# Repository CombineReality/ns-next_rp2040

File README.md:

# ns-next_rp2040
RP2040 Microcontroller board for North Star Next

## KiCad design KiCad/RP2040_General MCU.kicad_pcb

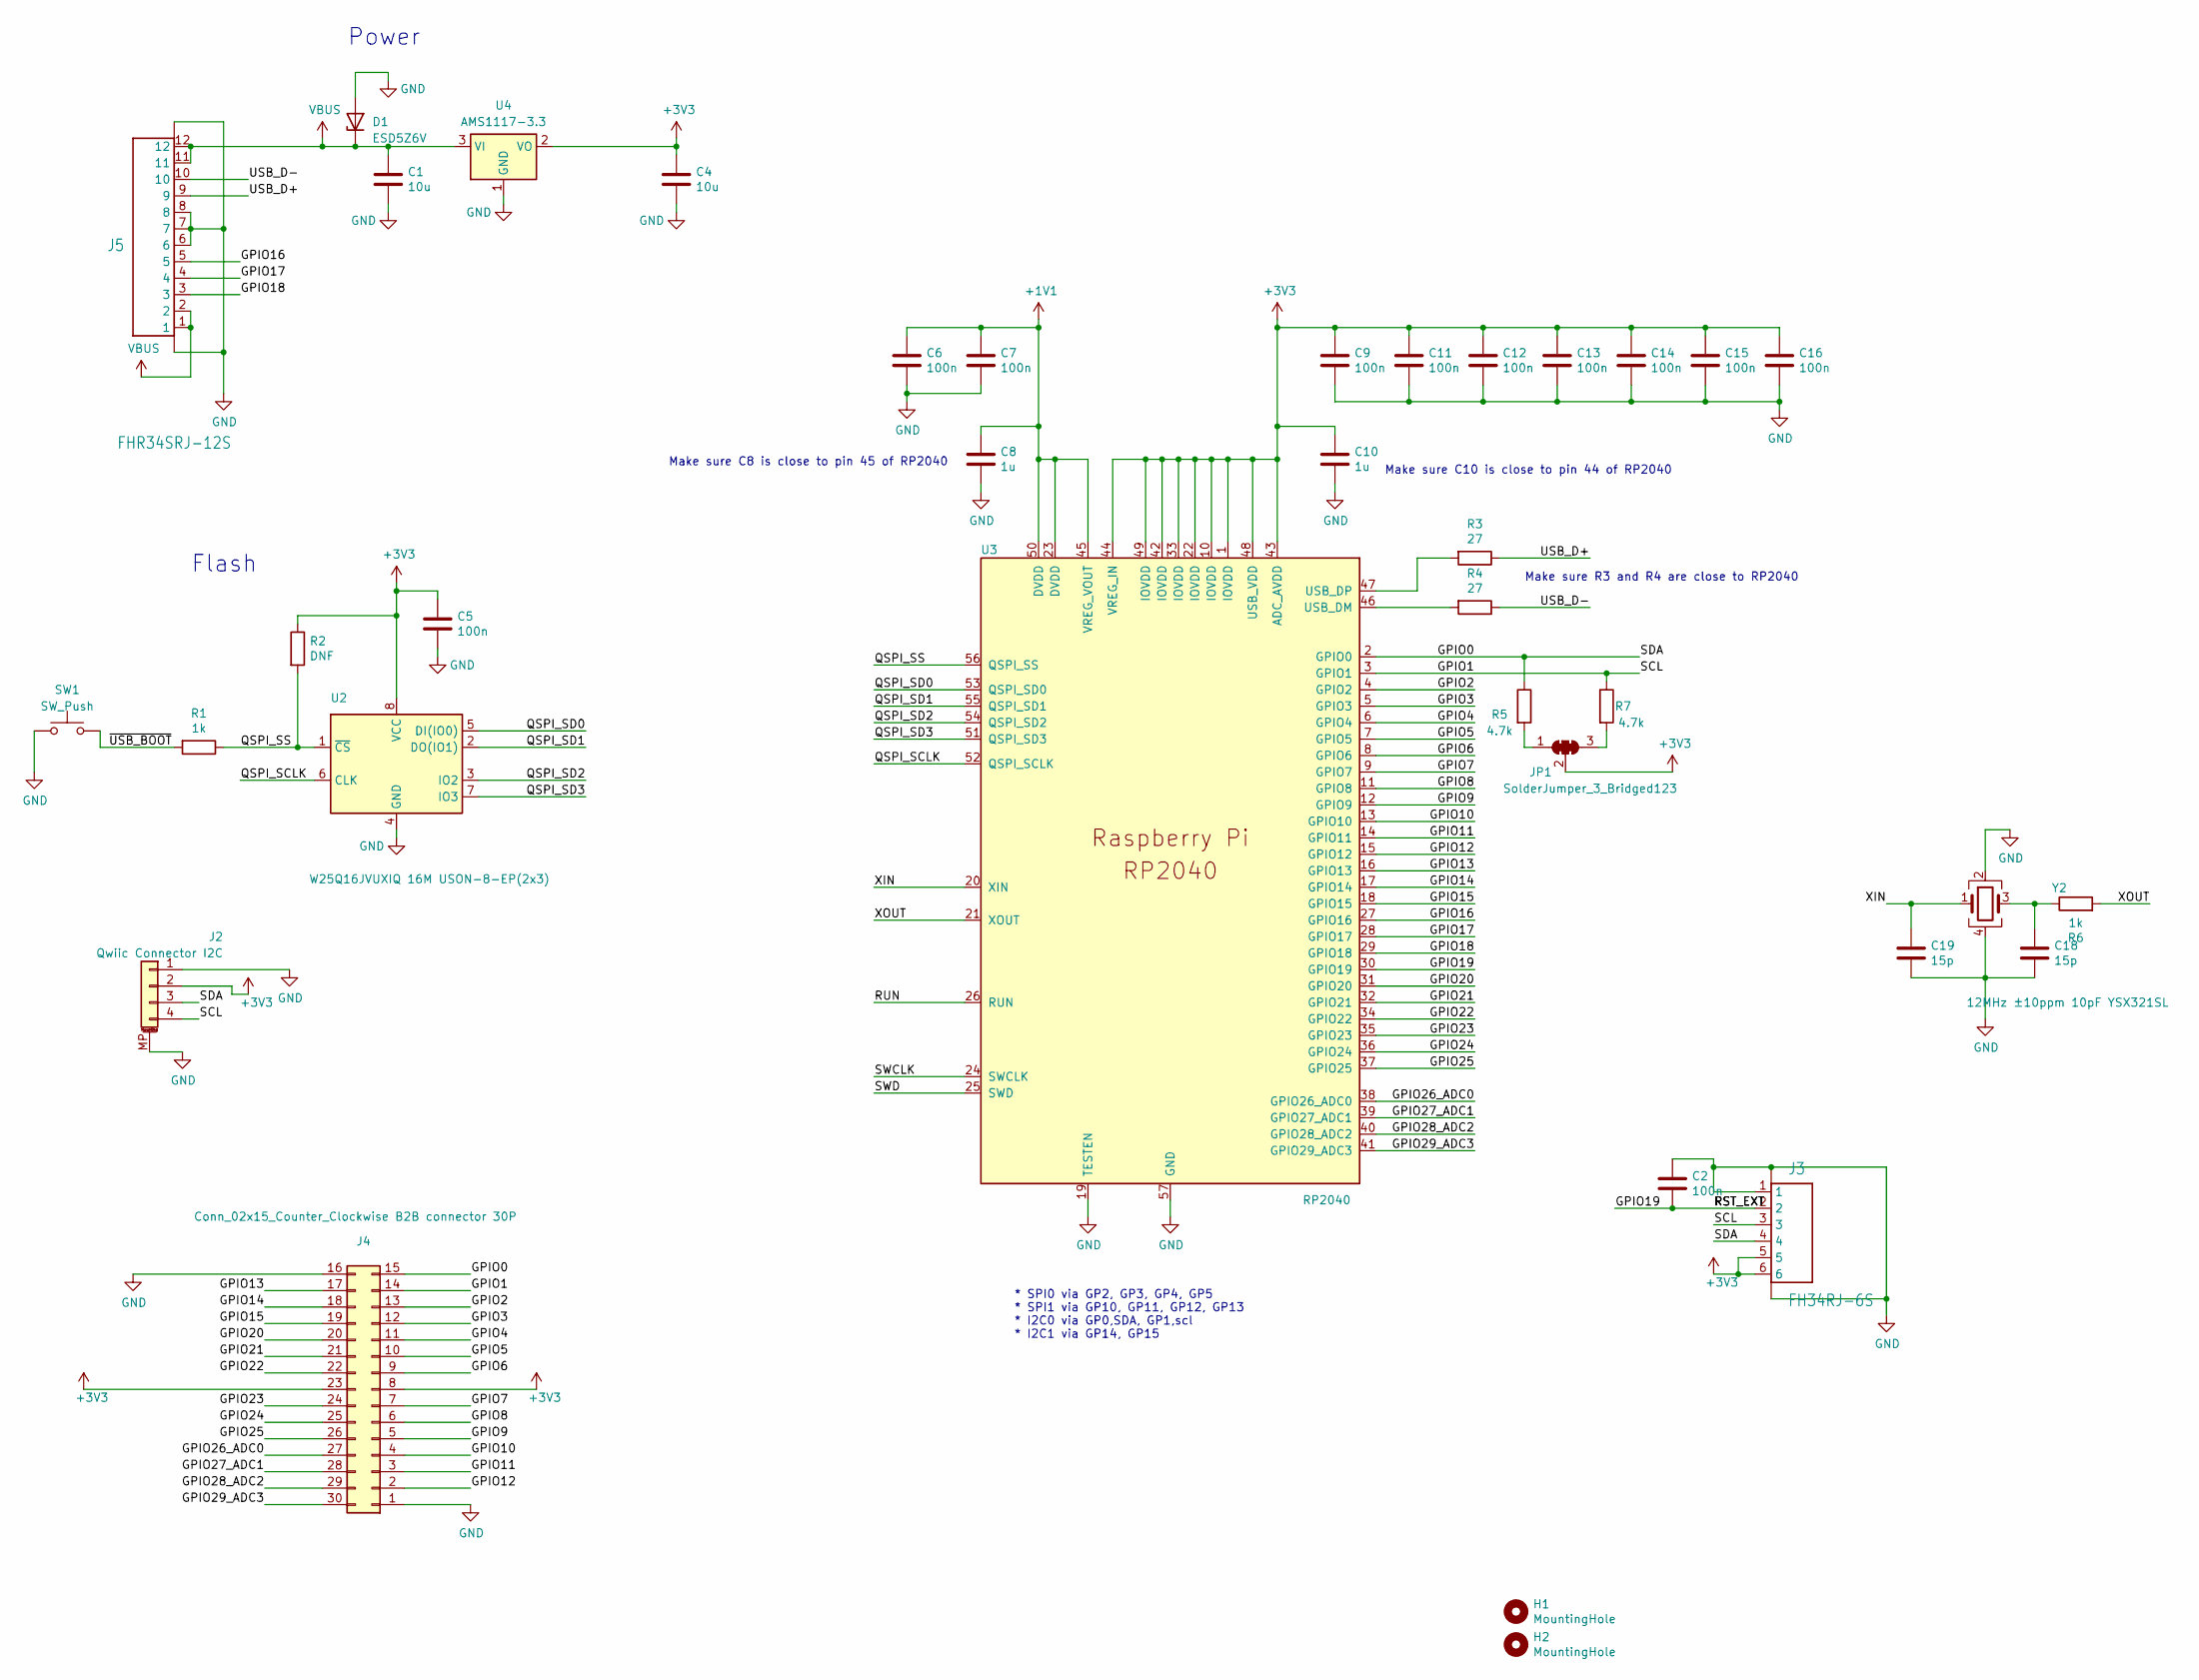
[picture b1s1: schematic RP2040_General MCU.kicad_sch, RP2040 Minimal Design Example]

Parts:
C1, C4: 10u; C_0805_2012Metric
C2, C5, C6, C7, C9, C11, C12, C13, C14, C15, C16: 100n; C_0402_1005Metric
C8, C10: 1u; C_0402_1005Metric
C18, C19: 15p; C_0402_1005Metric
D1: ESD5Z6V; D_SOD-523
H1, H2: MountingHole; MountingHole_2.2mm_M2
J2: Qwiic Connector I2C; JST_SH_SM04B-SRSS-TB_1x04-1MP_P1.00mm_Horizontal
J3: FH34RJ-6S
J4: Conn_02x15_Counter_Clockwise B2B connector 30P; BM20B(0.8)-30DS-0.4V(51)
J5: FHR34SRJ-12S; FPC-0.5-12P
JP1: SolderJumper_3_Bridged123; SolderJumper-3_P1.3mm_Open_RoundedPad1.0x1.5mm_NumberLabels
R1, R6: 1k; C_0402_1005Metric
R2: DNF; C_0402_1005Metric
R3, R4: 27; R_0402_1005Metric
R5, R7: 4.7k; C_0402_1005Metric
SW1: SW_Push; SW_Push_1P1T_NO_Vertical_Wuerth_434133025816
U2: W25Q16JVUXIQ 16M USON-8-EP(2x3); USON8_2X3MM
U3: RP2040; RP2040-QFN-56
U4: AMS1117-3.3; SOT-89-3
Y2: 12MHz ±10ppm 10pF YSX321SL; Crystal_SMD_3225-4Pin_3.2x2.5mm

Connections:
+1V1: C6.1, C7.1, C8.1, U3.23 (DVDD), U3.45 (VREG_VOUT), U3.50 (DVDD)
+3V3: C4.1, C5.1, C9.1, C10.1, C11.1, C12.1, C13.1, C14.1, C15.1, C16.1, J2.2, J3.5, J3.6, J4.8, J4.23, JP1.2 (C), R2.1, U2.8 (VCC), U3.1 (IOVDD), U3.10 (IOVDD), U3.22 (IOVDD), U3.33 (IOVDD), U3.42 (IOVDD), U3.43 (ADC_AVDD), U3.44 (VREG_IN), U3.48 (USB_VDD), U3.49 (IOVDD), U4.2 (VO)
/GPIO0: J2.3, J3.4, J4.15, R5.1, U3.2 (GPIO0)
/GPIO1: J2.4, J3.3, J4.14, R7.1, U3.3 (GPIO1)
/GPIO2: J4.13, U3.4 (GPIO2)
/GPIO3: J4.12, U3.5 (GPIO3)
/GPIO4: J4.11, U3.6 (GPIO4)
/GPIO5: J4.10, U3.7 (GPIO5)
/GPIO6: J4.9, U3.8 (GPIO6)
/GPIO7: J4.7, U3.9 (GPIO7)
/GPIO8: J4.6, U3.11 (GPIO8)
/GPIO9: J4.5, U3.12 (GPIO9)
/GPIO10: J4.4, U3.13 (GPIO10)
/GPIO11: J4.3, U3.14 (GPIO11)
/GPIO12: J4.2, U3.15 (GPIO12)
/GPIO13: J4.17, U3.16 (GPIO13)
/GPIO14: J4.18, U3.17 (GPIO14)
/GPIO15: J4.19, U3.18 (GPIO15)
/GPIO16: J5.5, U3.27 (GPIO16)
/GPIO17: J5.4, U3.28 (GPIO17)
/GPIO18: J5.3, U3.29 (GPIO18)
/GPIO19: C2.2, J3.2, U3.30 (GPIO19)
/GPIO20: J4.20, U3.31 (GPIO20)
/GPIO21: J4.21, U3.32 (GPIO21)
/GPIO22: J4.22, U3.34 (GPIO22)
/GPIO23: J4.24, U3.35 (GPIO23)
/GPIO24: J4.25, U3.36 (GPIO24)
/GPIO25: J4.26, U3.37 (GPIO25)
/GPIO26_ADC0: J4.27, U3.38 (GPIO26_ADC0)
/GPIO27_ADC1: J4.28, U3.39 (GPIO27_ADC1)
/GPIO28_ADC2: J4.29, U3.40 (GPIO28_ADC2)
/GPIO29_ADC3: J4.30, U3.41 (GPIO29_ADC3)
/QSPI_SCLK: U2.6 (CLK), U3.52 (QSPI_SCLK)
/QSPI_SD0: U2.5 (DI(IO0)), U3.53 (QSPI_SD0)
/QSPI_SD1: U2.2 (DO(IO1)), U3.55 (QSPI_SD1)
/QSPI_SD2: U2.3 (IO2), U3.54 (QSPI_SD2)
/QSPI_SD3: U2.7 (IO3), U3.51 (QSPI_SD3)
/QSPI_SS: R1.1, R2.2, U2.1 (~CS), U3.56 (QSPI_SS)
/RUN: U3.26 (RUN)
/SWCLK: U3.24 (SWCLK)
/SWD: U3.25 (SWD)
/USB_D+: J5.9, R3.1
/USB_D-: J5.10, R4.1
/XIN: C19.1, U3.20 (XIN), Y2.1
/XOUT: R6.2, U3.21 (XOUT)
/~USB_BOOT: R1.2, SW1.2
GND: C1.2, C2.1, C4.2, C5.2, C6.2, C7.2, C8.2, C9.2, C10.2, C11.2, C12.2, C13.2, C14.2, C15.2, C16.2, C18.2, C19.2, D1.2 (A), J2.1, J2.MP (MountPin), J3.1, J3.MH1 (G1), J3.MH2 (G2), J4.1, J4.16, J5.6, J5.7, J5.8, J5.P$13 (G1), J5.P$14 (G2), SW1.1, U2.4 (GND), U3.19 (TESTEN), U3.57 (GND), U4.1 (GND), Y2.2, Y2.4
unnamed: C18.1, R6.1, Y2.3
unnamed: JP1.1 (A), R5.2
unnamed: JP1.3 (B), R7.2
unnamed: R4.2, U3.46 (USB_DM)
unnamed: R3.2, U3.47 (USB_DP)
VBUS: C1.1, D1.1 (K), J5.1, J5.2, J5.11, J5.12, U4.3 (VI)

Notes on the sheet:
Power
Flash
Make sure C10 is close to pin 44 of RP2040
Make sure R3 and R4 are close to RP2040
* SPI0 via GP2, GP3, GP4, GP5 * SPI1 via GP10, GP11, GP12, GP13 * I2C0 via GP0,SDA, GP1,scl * I2C1 via GP14, GP15
Make sure C8 is close to pin 45 of RP2040

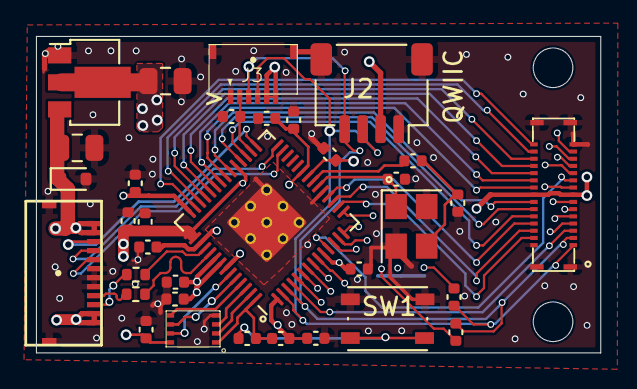
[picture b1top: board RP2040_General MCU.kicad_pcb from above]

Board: 4 copper layers, 31.3 x 17.6 mm, 37 parts (1 on the bottom side), 50 nets.

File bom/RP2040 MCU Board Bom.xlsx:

id | Sourced | References | Value | Footprint | Quantity
1 |  | C2, C5, C6, C7, C9, C11, C12, C13, C14, C15, C16 | 100n | C_0402_1005Metric | 11
2 |  | C1, C4 | 10u | C_0805_2012Metric | 2
3 |  | C8, C10 | 1u | C_0402_1005Metric | 2
4 |  | C18, C19 | 15p | C_0402_1005Metric | 2
5 |  | R1, R6 | 1k | C_0402_1005Metric | 2
6 |  | R3, R4 | 27 | R_0402_1005Metric | 2
7 |  | R5, R7 | 4.7k | C_0402_1005Metric | 2
8 |  | R2 | DNF | C_0402_1005Metric | 1
9 |  | D1 | ESD5Z6V | D_SOD-523 | 1
10 |  | U2 | W25Q32JVUUIQ 32M USON-8 | USON8_2X3MM | 1
11 |  | U3 | RP2040 | RP2040-QFN-56 | 1
12 |  | U4 | AMS1117-3.3 | SOT-89-3 | 1
13 |  | Y2 | Crystal_GND24 YSX321SL 12MHz 卤10ppm 9pF | Crystal_SMD_3225-4Pin_3.2x2.5mm | 1
14 |  | SW1 | SW_Push | SW_Push_1P1T_NO_Vertical_Wuerth_434133025816 | 1
15 |  | H1, H2 | MountingHole | MountingHole_2.2mm_M2 | 2
16 |  | JP1 | SolderJumper_3_Bridged123 | SolderJumper-3_P1.3mm_Open_RoundedPad1.0x1.5mm_NumberLabels | 1
17 |  | J2 | Qwiic Connector I2C | JST_SH_SM04B-SRSS-TB_1x04-1MP_P1.00mm_Horizontal | 1
18 |  | J3 | FH34RJ-6S | FH34RJ-6S | 1
19 |  | J4 | Conn_02x15_Counter_Clockwise B2B connector 30P | BM20B(0.8)-30DS-0.4V(51) | 1
20 |  | J5 | FHR34SRJ-12S | FPC-0.5-12P | 1

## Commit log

2024-05-11 Added KiCad and iBom files
